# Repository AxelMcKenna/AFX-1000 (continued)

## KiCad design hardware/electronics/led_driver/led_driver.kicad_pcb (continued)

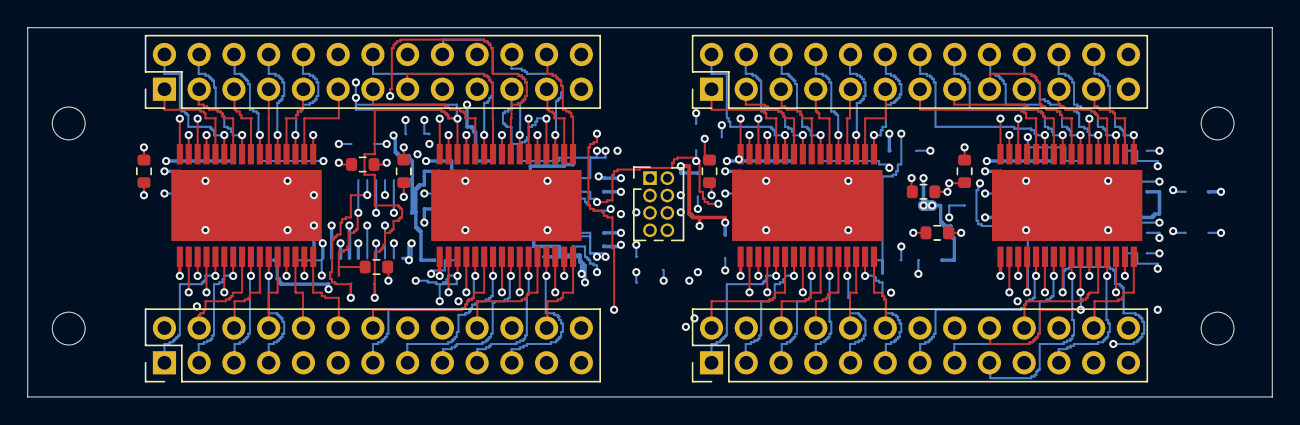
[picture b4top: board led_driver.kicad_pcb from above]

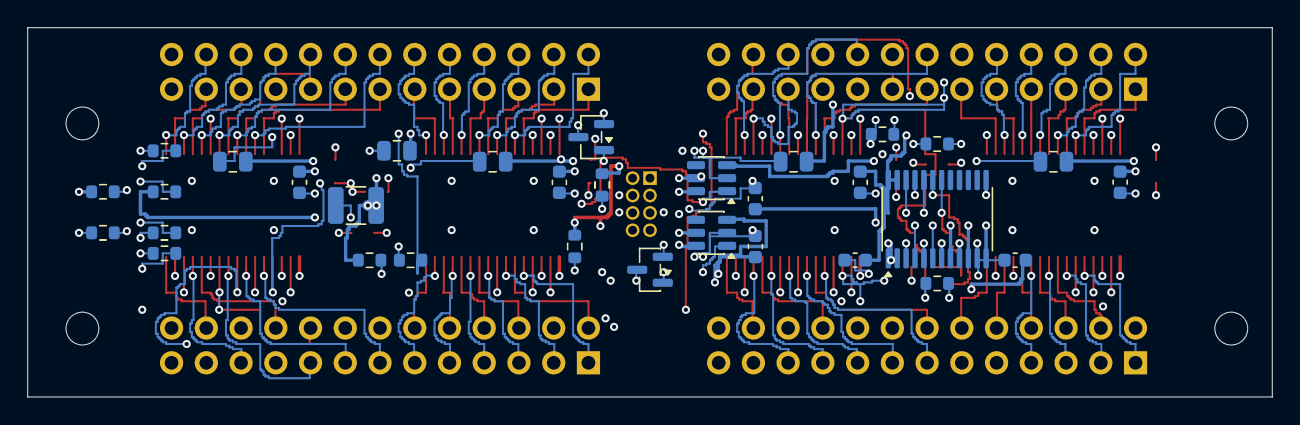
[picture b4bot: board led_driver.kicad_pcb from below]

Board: 6 copper layers, 91.0 x 27.0 mm, 53 parts (32 on the bottom side), 122 nets.

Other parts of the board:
H1, H2, H3, H4: M2_CLEARANCE; M2_Insert_Clearance

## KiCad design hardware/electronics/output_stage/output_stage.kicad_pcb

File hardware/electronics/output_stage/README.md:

# E05 circuit / E07 routed stereo output board

E05 is the native KiCad schematic for the post-receiver line drivers and stereo
gain-output relay: 41 components, fixed-feedback master/consumer amplifiers,
separate coupling/bleed networks and the E02/E03 interfaces. E07 is a **routed,
unassembled output-stage prototype**, not the complete analog/power design.

The [native E07 PCB](output_stage.kicad_pcb) is 82 × 34 × 1.6 mm with four copper
layers, 211 track segments and 45 through vias. The
[routing check](generated/routing-verification.json) passes all-severity native
DRC/library/parity with **zero violations and zero open connections**. KiCad
refills and saves the analog reference plane before the check. Native
[top](generated/placement-top.svg), [bottom](generated/placement-bottom.svg),
[reference plane](generated/reference-plane.svg) and
[inner routing](generated/inner-routing.svg) views show the actual saved board.
This electrical layout check does not establish fabrication readiness or audio
performance; final stackup, passive/connector selection and bench work remain open.

Open [the native project](output_stage.kicad_pro),
[schematic SVG](generated/output_stage.svg), [BOM](bom.csv),
[connection schedule](components.json) or
[verification record](generated/verification.json). The
[circuit analysis](generated/circuit-analysis.json) uses the actual exported
netlist and explicitly identifies its ideal-device assumptions.
The [A03/E07 review package](../../cad/generated/standalone-review-A03-E07.zip)
includes the current hardware sources, native projects, CAD and check records.
Standard KiCad/OpenSCAD and the documented Python packages remain external.

## Circuit and boundary

J1 requires a low-impedance, nominal 2 V RMS full-scale **single-ended** signal
nominally centered on 0 V after the DAC's I/V and differential receiver/filter.
It is not an interface to the raw codec differential pins. The
[E08 receiver prototype](../dac_receiver/README.md) proposes a ±25 mV DC
allocation and checks that allowance against the E05 peak-margin screen. The
original ideal E05 calculations use zero DC; physical scale, calibration and
power behavior remain unverified. Keep its source impedance
at or below 100 Ω; R17/R18 provide 100 kΩ bias returns.

Both drivers run continuously. U1, OPA2992D on regulated ±19 V, supplies Master
gain 6.23 using 5.23 kΩ/1 kΩ feedback. U2, OPA1612AID on regulated ±12 V, supplies
Send/Return gain 1.605 using 1.21 kΩ/2 kΩ feedback. The consumer resistor scale
keeps the feedback and output loads together above 2 kΩ. Feedback stays connected
regardless of the gain relay position.

Each branch has 100 Ω series resistance, two parallel 4.7 µF nonpolar film
capacitors and a 20 kΩ discharge resistor. K3 selects Master through its NC
contacts or Send/Return through its NO contacts; it never directly joins the
two amplifier outputs. Separate coupling networks let both branches retain
their own DC settling. Capacitors block DC in the ideal model; leakage,
dielectric behavior and switching transients require measurement.

| Interface | Pins / connection |
| --- | --- |
| J1 post-receiver input | 1:Left, 2:AGND, 3:Right; 2 V RMS nominal full scale, zero DC |
| J2 processed output | 1:Left, 2:AGND, 3:Right → E03 J3 pins 4/5/6 |
| J3 gain coil | 1:5 V, 2:GAIN_LOW → E02 J5 pins 1/2 |
| J4 regulated supplies | 1:+19 V, 2:AGND, 3:−19 V, 4:+12 V, 5:−12 V |

The second gain relay, for stereo input-range selection, is external and must
share E02's gain driver as planned. Firmware D9 stays low for Master and high
for Send/Return; the existing dry-wait/gain-settle/rearm sequence still applies.
This sheet does not contain a second driver or another flyback clamp.

**All four analog rails** must qualify E02 ANALOG_OK, independently of firmware.
Loss of the ±12 V pair can invalidate the selected consumer output and receiver
even if ±19 V remains healthy. Exact supervisors, thresholds, sequencing and
power-down margins remain unselected. Use the digital/power return for the coil
current; resolve analog reference and shield connections in the integrated PCB.

±12 V gives the low-voltage receiver/driver domain room for the prospective ADC
driver; its final load remains to be calculated. This choice does not approve
the complete analog power budget. OPA1612 must not use the ±19 V rails.

## Calculated results and limits

With nominal parts, an ideal 2 V RMS input and a combined external 10 kΩ load:

| Result | Master | Send/Return |
| --- | ---: | ---: |
| Output at 1 kHz | 12.276 V RMS | 3.163 V RMS |
| Scale error against E01 target | −0.0050 dB | +0.0008 dB |
| Effective amplifier resistive load | 3.244 kΩ | 2.177 kΩ |
| Passive coupling loss at 20 Hz relative to 1 kHz | −0.0674 dB | −0.0674 dB |

The 20 kΩ bleed and the external load are both included. Tolerance analysis
enumerates all 64 sign combinations per branch, 256 total: 0.1% feedback/ground,
1% series/bleed and 10% for each coupling capacitor. At a fixed 10 kΩ external
load, calculated scale error stays within 0.022 dB, the passive 20 Hz coupling
loss stays below 0.084 dB and the amplifier load remains above 2 kΩ.

These are output-stage calculations. Receiver scale/loading and the full unit's
gain error are not verified. The 10 kΩ limit is the **combined** external load
of all parallel output connectors; smaller loads need a new review.

The rail screen includes 1% supply tolerance, worst feedback tolerances and a
1% high full-scale input. It leaves about 0.68 V of peak margin for Master with
an assumed 0.3 V amplifier rail reserve. That reserve is from OPA2992's 40 V/2 kΩ
table; its use at the planned 38 V supply is still a screening assumption.
The consumer screen uses OPA1612's 0.6 V reserve at 2 kΩ. Neither establishes
real clipping, distortion or capacitive-load stability.

The illustrative white-density output-noise estimates are approximately
6.88 µV RMS for Master and 0.89 µV for Send/Return over 20 Hz–20 kHz, unweighted.
They include passive coupling and bleed noise but omit 1/f noise, receiver/source
noise, supplies, PCB coupling and part spread. Do not combine these directly
with A-weighted codec figures or claim a passing whole-unit S/N result.

An ideal class-B/quiescent-power screen gives approximately 0.26 W for the
master dual package and 0.29 W for the consumer dual package. Reference thermal
resistances imply substantial temperature rise; actual board copper, airflow,
internal ambient and temperatures remain to be measured. There is no validated
short-circuit or overload rating for the output resistors or complete stage.

## Capacitors and housing impact

The reviewed WIMA MKS2 drawing is revision 03.26. It lists
MKS2C044701O00KSSD, 4.7 µF/63 V/10%, with a 7.2 × 11 × 18 mm nominal body,
5 mm lead pitch and nominal 0.5 mm leads. Each branch uses two in parallel for
9.4 µF. The earlier 10 µF/50 V part is absent from this current drawing and is
not used in E05. The [source record](dependencies.json) captures the PDF hash.

The standard footprint's actual 5 mm pitch and 0.8 mm drill are checked. Its
nominal plan size is a candidate; maximum body/lead tolerances, standoff,
courtyard and printed assembly still need fit checks. Its generic 3D model does
not prove the 18 mm height. The former A02 12 mm audio reserve did not contain
these parts. A03 now uses the E07 placement packet, lowers the board to Z=3.8,
adds a floor recess and staggers the capacitor pairs to clear scene controls.
The [CAD report](../../cad/generated/solid-validation.json) records empty
intersection with the modeled shell/controls, including switch-lead and
scene-PCB allowances. This remains conditional on the documented dimensions
and assembly limits, with physical fit unverified.

The [actual-PCB mechanical packet](generated/placement.json) includes all 41
component and 29 through-hole solder/lead reserves. The four series resistors,
four bleed resistors and C8 sit on the back. Trim through-hole protrusions,
including solder, to ≤1.5 mm. Qualify the underside resistor/capacitor height
limits and the remaining generic passive MPNs before assembly.

Four Ø2.4 mounting holes match the CAD's Ø7.2 bosses and Ø3.2 through bores for
CNC Kitchen M2 × 3 inserts. Through bores accommodate the short boss stack; the
insert is flush, with M2 × 4 board screws. The floor recess leaves 1.6 mm of
plastic. Actual bore/insert fit, wall/floor stiffness and screw engagement remain
physical checks. The converter/input and final power-board placements are open.

## Native checks and remaining integration

Routing is explicit in [route.py](route.py). Feedback stays on the top layer
near the amplifiers; the four coupled branches stay separate until K3. R10
moves down to avoid taking its ground pad across the consumer-left feedback
path. F.Cu/B.Cu carry most audio traces, In1.Cu is the AGND reference plane,
and In2.Cu carries the inputs, supply trunks, a short output crossing and the
separate two-wire coil circuit. Coil current returns only through E02's driver.
The routing uses 0.3–0.6 mm tracks and Ø0.7/0.3 mm through vias, with a 0.25 mm
minimum clearance. No blind vias, via-in-pad assembly process or buried vias are
required. The fabrication house's actual four-layer materials and copper weights
are still to be selected; the present 1.6 mm thickness is a mechanical contract.

Local bypasses follow the amplifier supply pins. The longer signal paths,
single reference plane, return currents, supply impedance, thermal behavior and
coil switching still require review and measurement on the assembled board.
Native DRC does not verify signal integrity, stability, S/N or switching clicks.

    python3 -m hardware.electronics.output_stage.generate
    python3 -m hardware.electronics.output_stage.place --kicad-cli /path/to/kicad-cli
    python3 -m hardware.electronics.output_stage.route
    python3 -m hardware.electronics.output_stage.verify --kicad-cli /path/to/kicad-cli
    python3 -m hardware.electronics.output_stage.check_placement --kicad-cli /path/to/kicad-cli
    python3 -m hardware.cad.standalone

The verifier runs all-severity native KiCad ERC and checks every exported pin
against an independent contract. Fresh E02/E03 exports confirm the harnesses.
A complex nodal solver checks both channels and both relay states at 20 Hz,
1 kHz and 20 kHz: 12 ideal AC cases, with four further ideal DC-blocking cases.
The analytical gain/filter expressions are compared against that circuit solve.
The checks do not run a semiconductor SPICE model or measure real crosstalk.

Standard libraries remain external; --footprint-dir can locate them. Source and
library hashes are recorded. Generation replaces the native schematic, so
persist circuit edits in generate.py while using this workflow.
Persist footprint positions and board datums in place.py. It regenerates the
board and overwrites direct PCB edits. route.py adds/replaces generated copper;
it accepts both the initial legacy file and KiCad 10's normalized saved file.
check_placement.py refills/saves the actual board, requires all native DRC/parity
and connectivity results to be clear, and exports the mechanical packet;
standalone.py rejects
a packet whose PCB hash is stale. Standard footprints are embedded in the PCB
as in a normal KiCad board; their external libraries are not vendored. The local
mounting footprint is original project geometry. For a deliberately placed-only
intermediate, check_placement.py --unrouted retains and reports open connections;
it cannot label that state as routed. The earlier placement-drc.json is retained
as historical E06 evidence; routing-drc.json is the current native result.

Complete the converter/receiver, stereo input protection/range stage, regulators,
all rail supervisors, final connectors, ESD and integrated PCB before fabrication.
Then measure frequency response, calibrated gain, noise/THD, clipping, DC/clicks,
hot-plug, capacitive loads, output shorts, power loss and actual temperatures.
Prototype header footprints, some passive MPNs and capacitor bias curves remain
selection gates. E07 routing is complete for this output subassembly. No board
has been ordered, fabricated, assembled or released as the complete unit.

Primary sources: [OPA2992](https://www.ti.com/lit/ds/symlink/opa2992.pdf),
[OPA1612](https://www.ti.com/lit/ds/symlink/opa1612.pdf),
[WIMA MKS2](https://wima.de/wp-content/uploads/media/e_WIMA_MKS_2.pdf),
[Omron G6K](https://omronfs.omron.com/en_US/ecb/products/pdf/en-g6k.pdf).

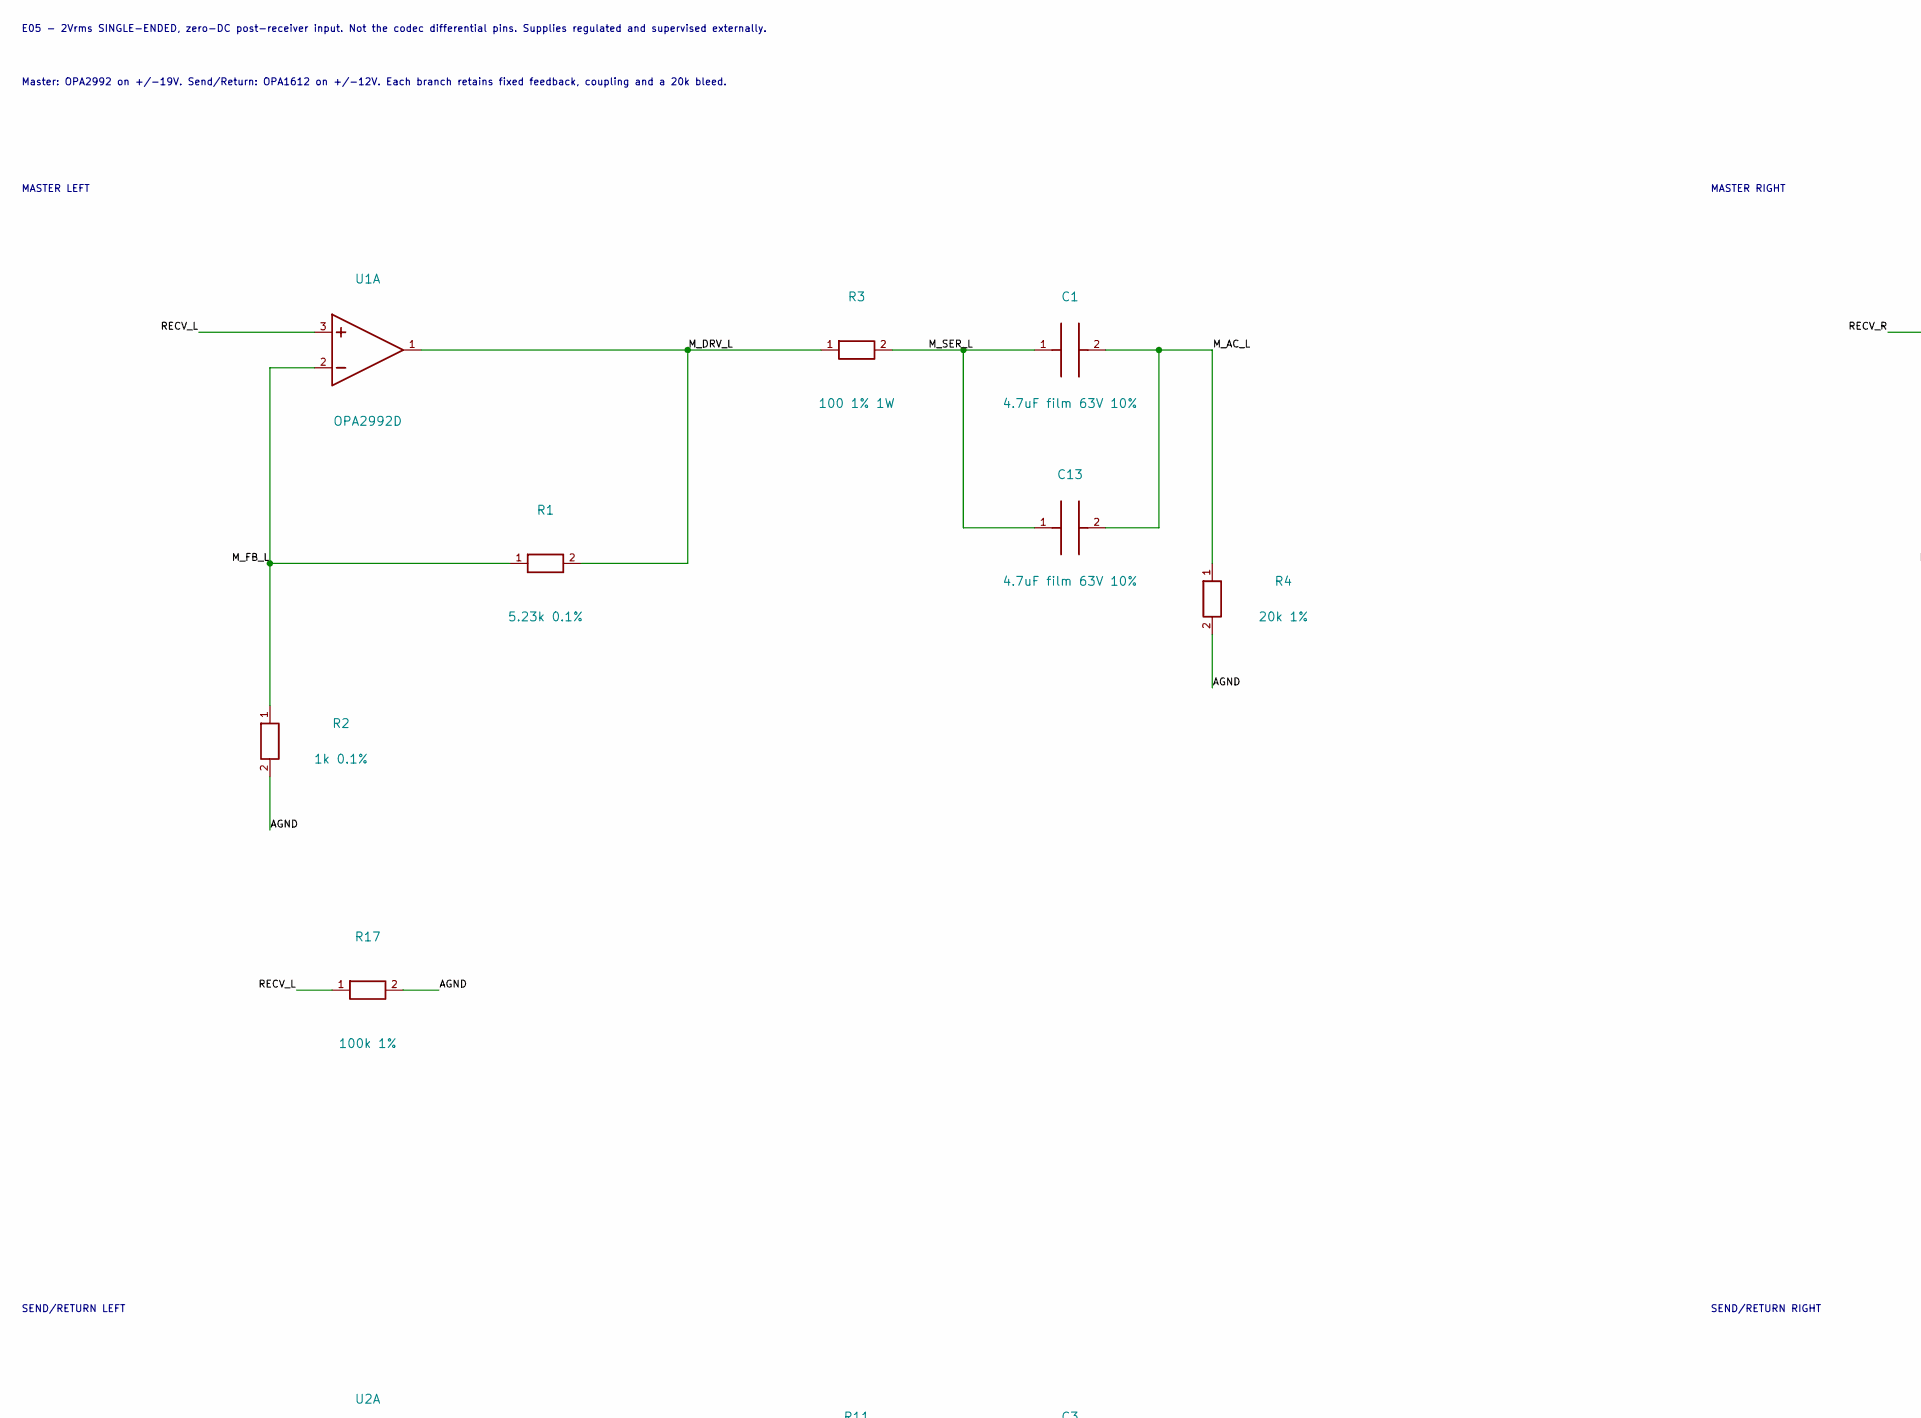
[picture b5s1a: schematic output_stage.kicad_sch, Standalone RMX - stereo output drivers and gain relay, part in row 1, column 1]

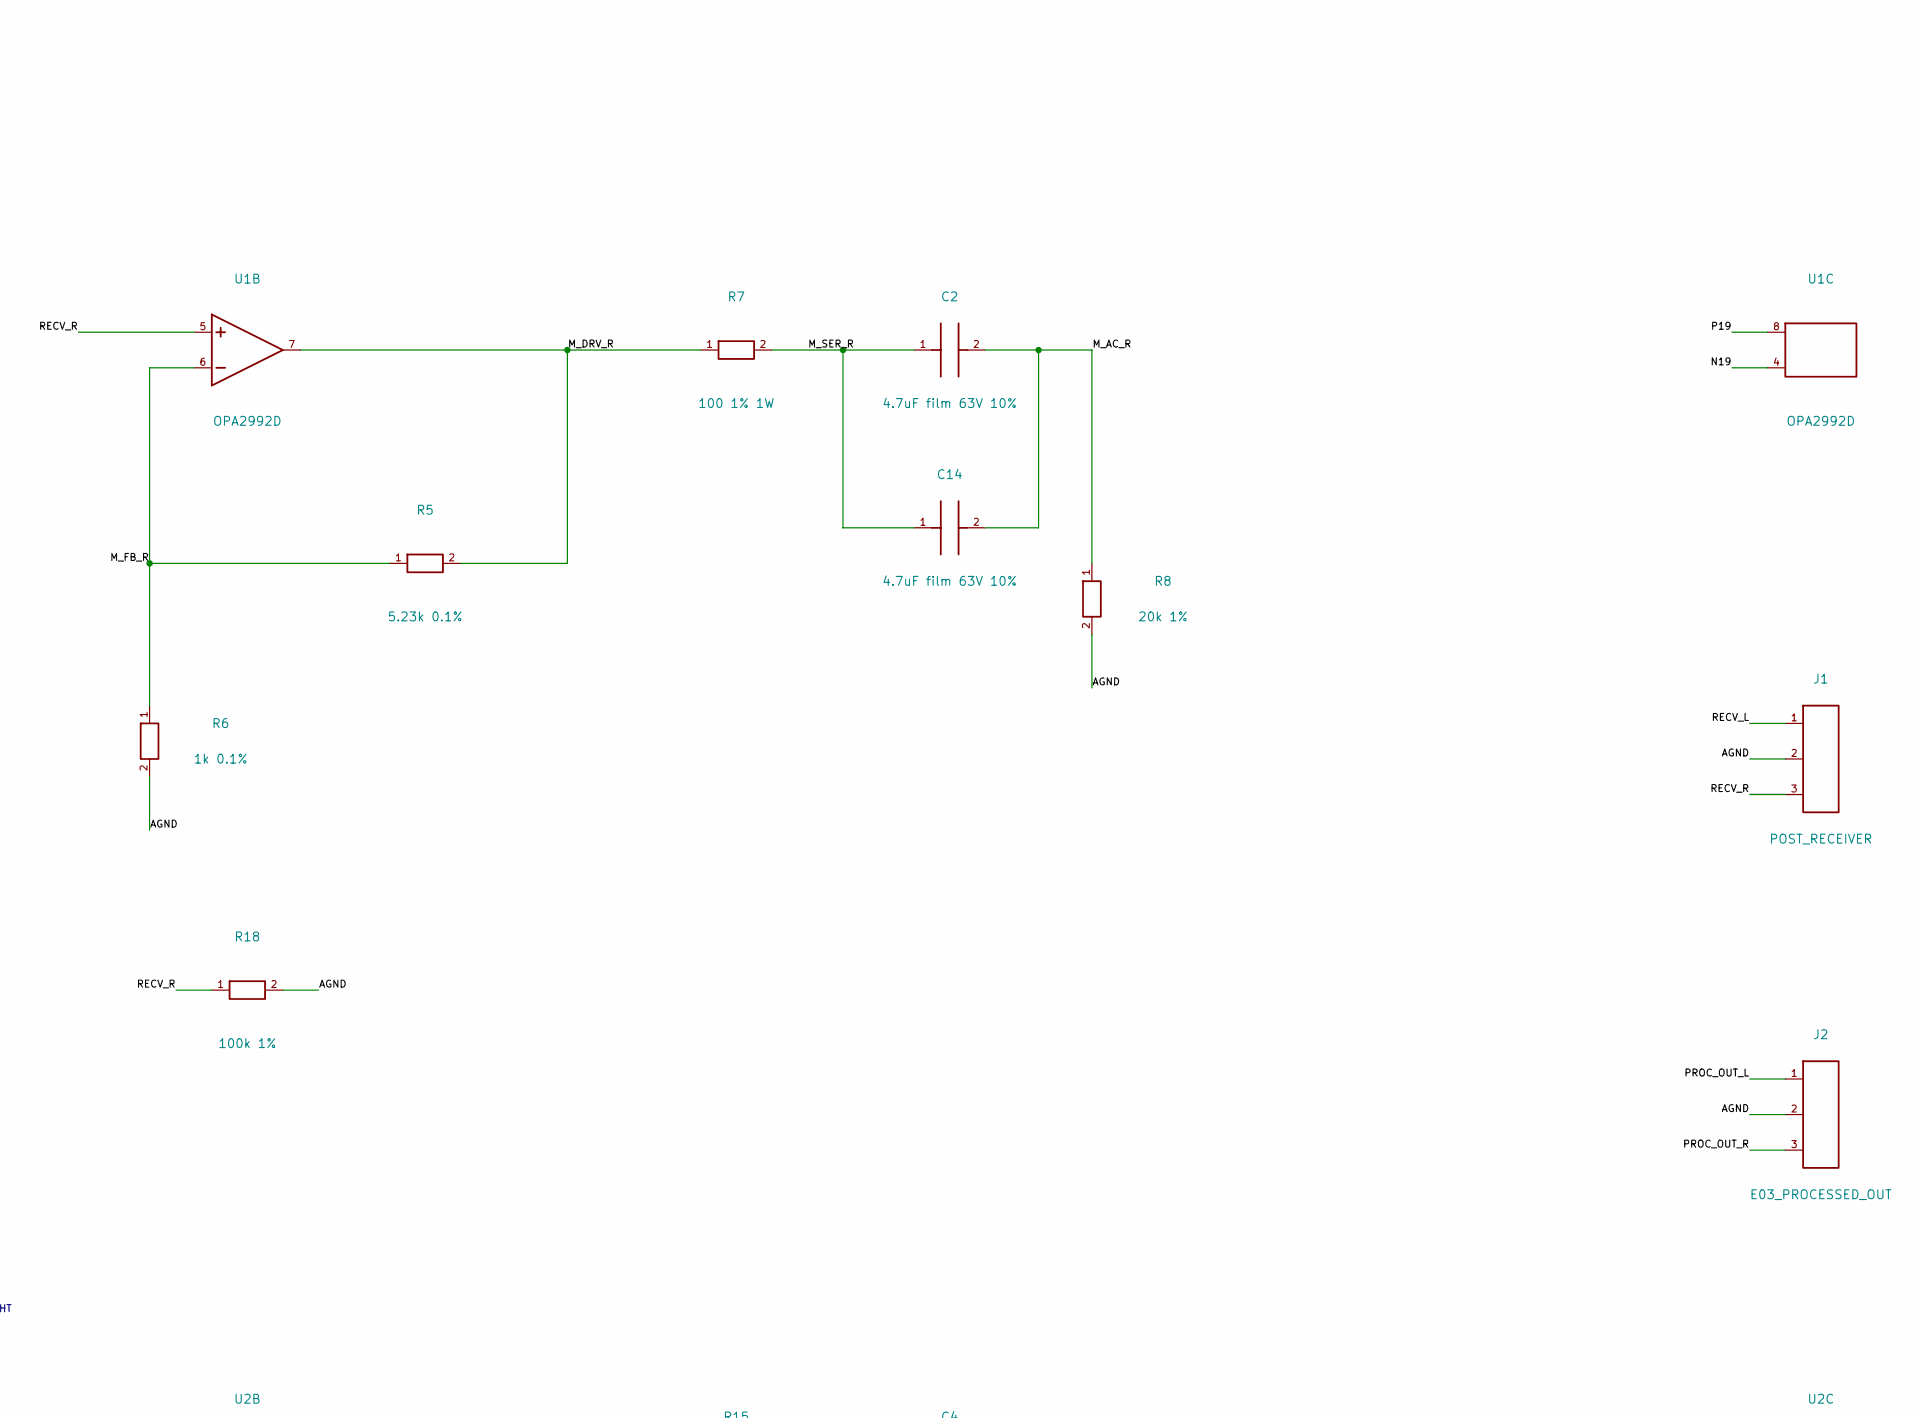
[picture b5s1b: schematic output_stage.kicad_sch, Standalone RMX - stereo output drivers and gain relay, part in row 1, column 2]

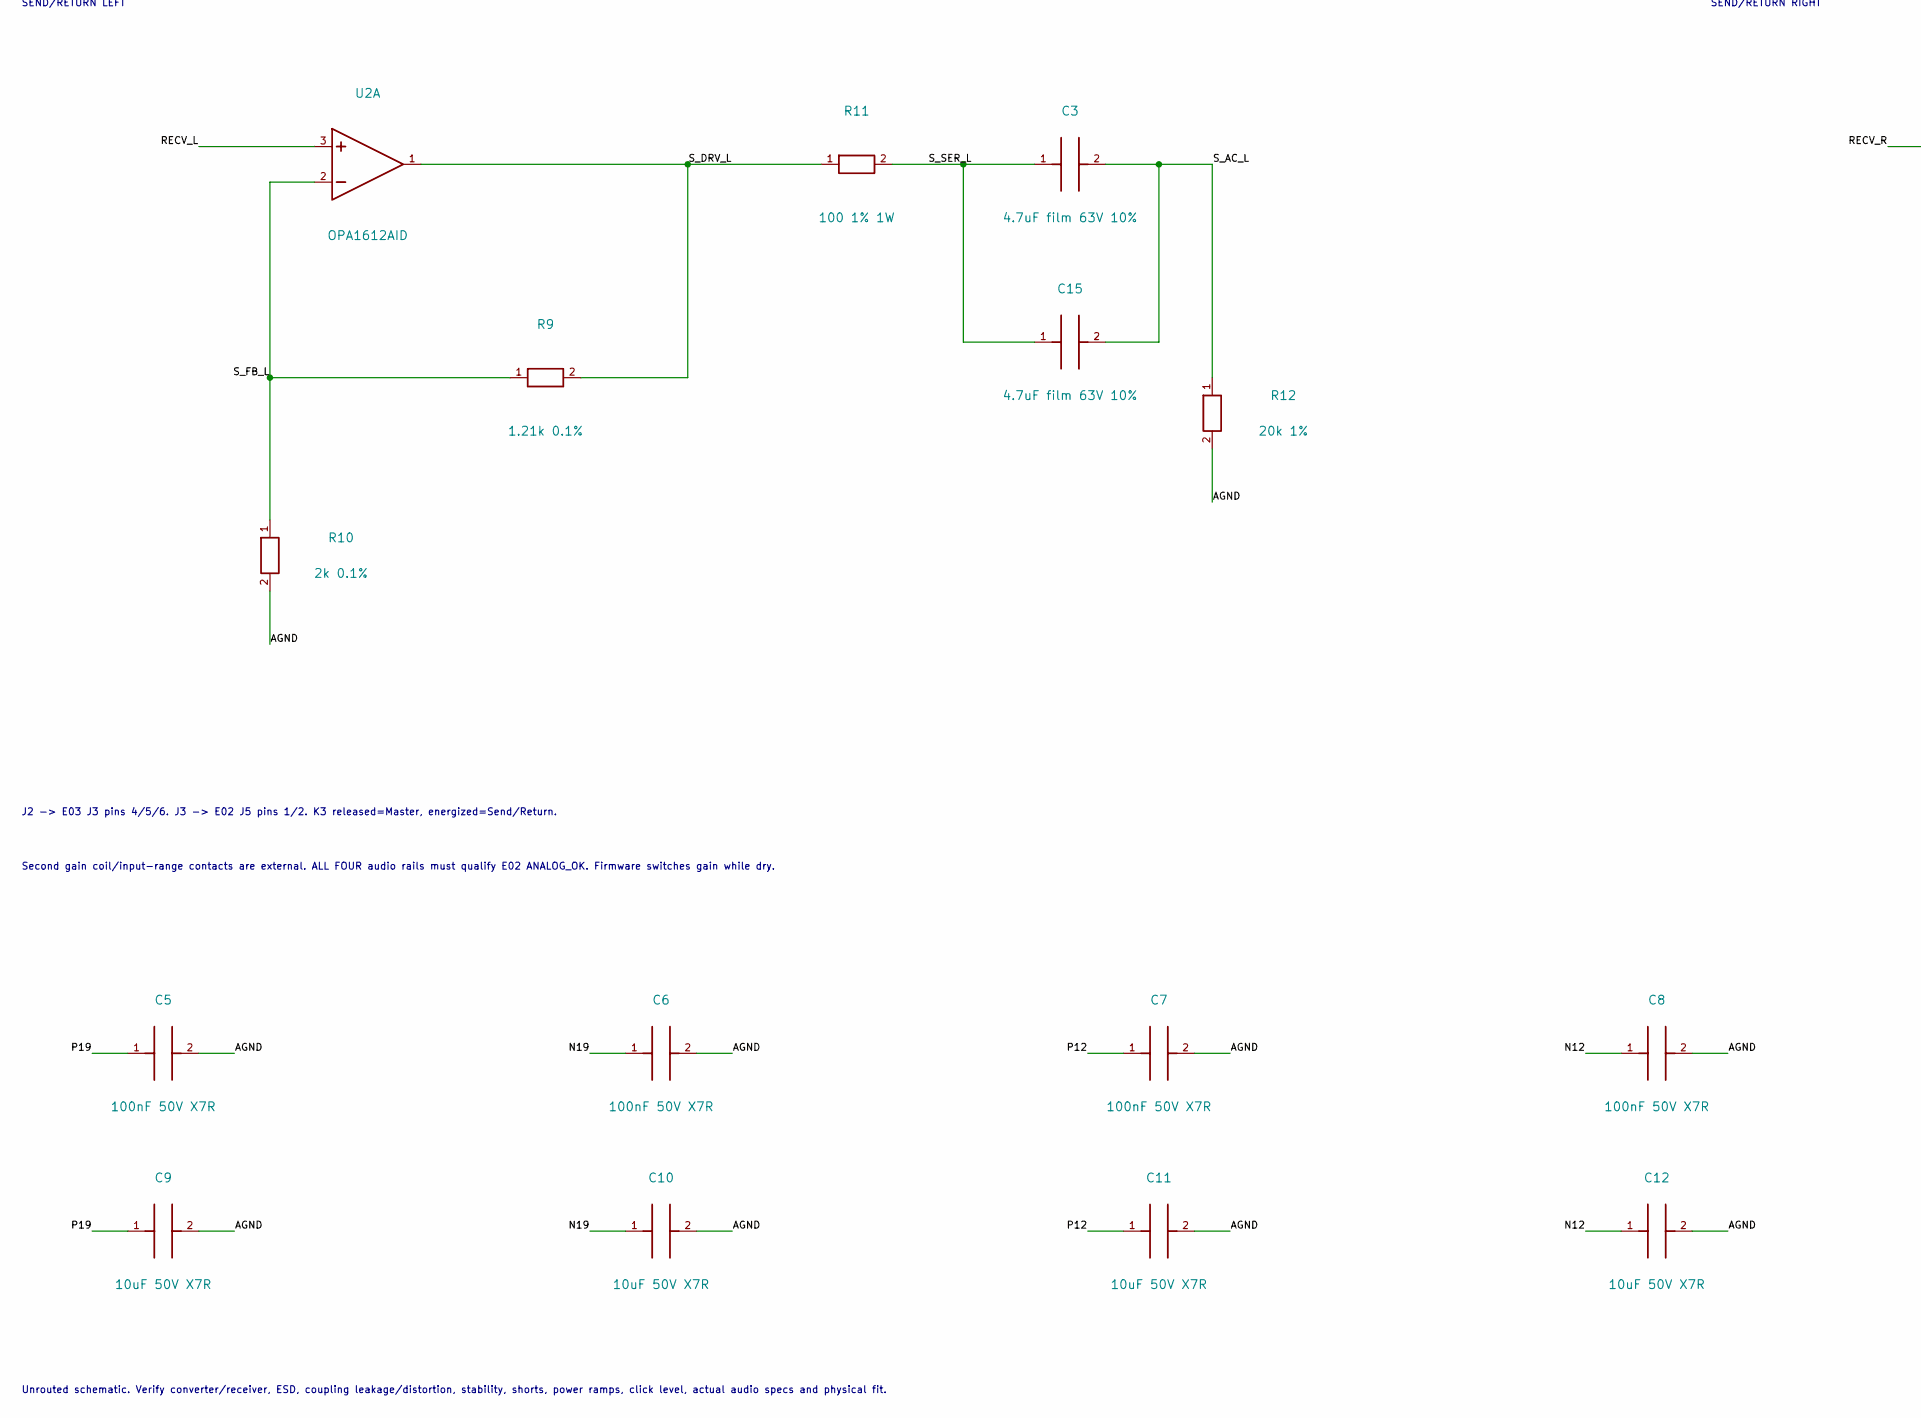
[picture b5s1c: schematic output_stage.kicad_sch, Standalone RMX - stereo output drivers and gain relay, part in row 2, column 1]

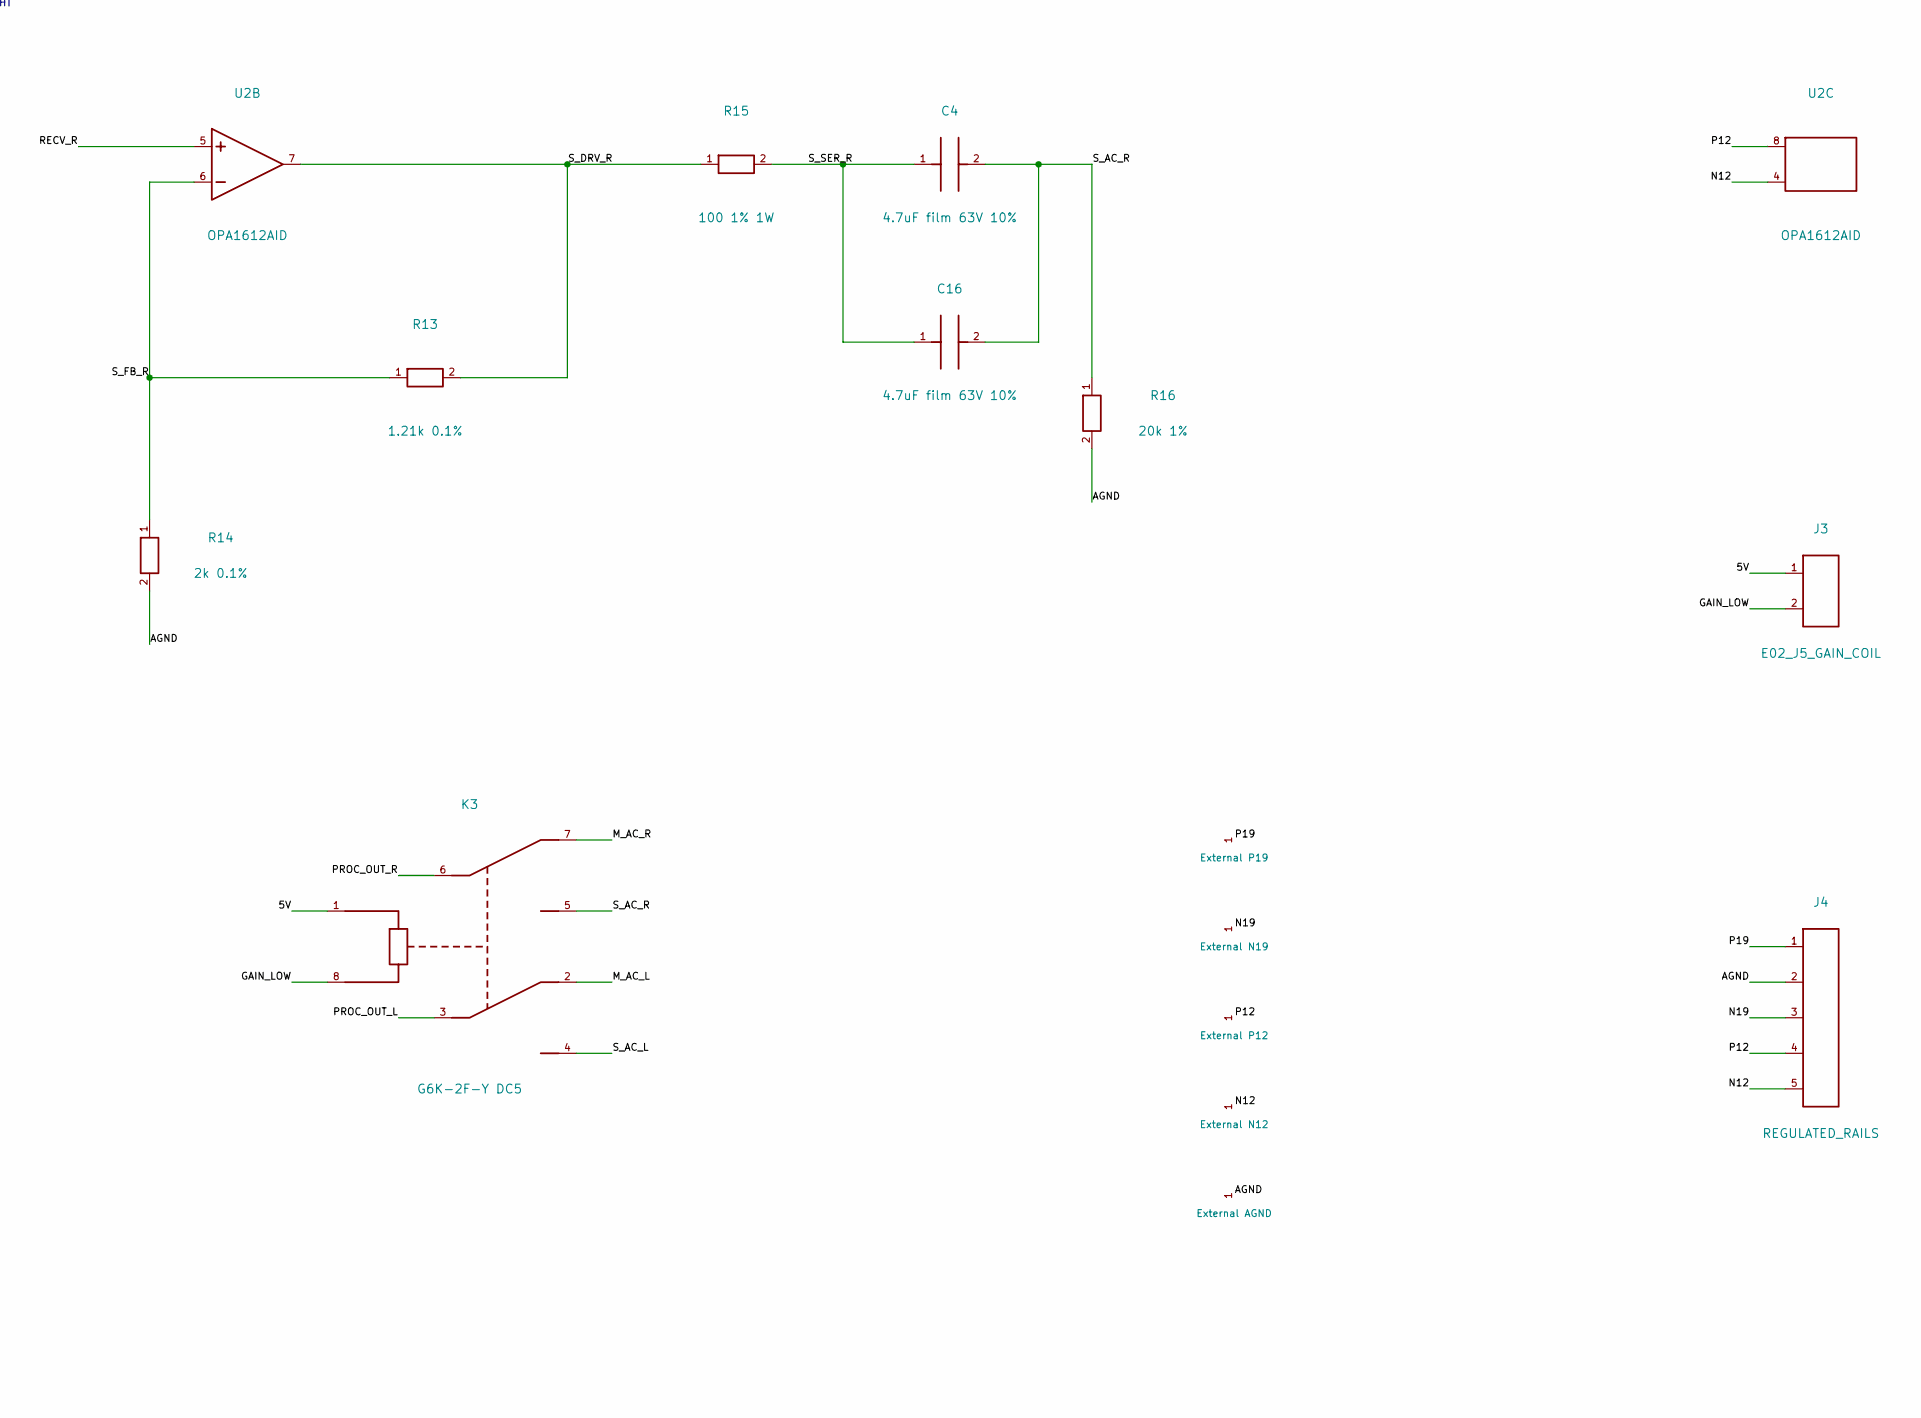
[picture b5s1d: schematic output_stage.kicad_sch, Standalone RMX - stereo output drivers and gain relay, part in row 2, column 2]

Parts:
C1, C2, C3, C4, C13, C14, C15, C16: 4.7uF film 63V 10%; C_Rect_L7.2mm_W11.0mm_P5.00mm_FKS2_FKP2_MKS2_MKP2; MPN MKS2C044701O00KSSD
C5, C6, C7, C8: 100nF 50V X7R; C_0805_2012Metric
C9, C10, C11, C12: 10uF 50V X7R; C_1210_3225Metric
J1: POST_RECEIVER; PinHeader_1x03_P2.54mm_Vertical
J2: E03_PROCESSED_OUT; PinHeader_1x03_P2.54mm_Vertical
J3: E02_J5_GAIN_COIL; PinHeader_1x02_P2.54mm_Vertical
J4: REGULATED_RAILS; PinHeader_1x05_P2.54mm_Vertical
K3: G6K-2F-Y DC5; Relay_DPDT_Omron_G6K-2F-Y; MPN G6K-2F-Y DC5
R1, R5: 5.23k 0.1%; R_0805_2012Metric
R2, R6: 1k 0.1%; R_0805_2012Metric
R3, R7, R11, R15: 100 1% 1W; R_2512_6332Metric
R4, R8, R12, R16: 20k 1%; R_0805_2012Metric
R9, R13: 1.21k 0.1%; R_0805_2012Metric
R10, R14: 2k 0.1%; R_0805_2012Metric
R17, R18: 100k 1%; R_0805_2012Metric
U1: OPA2992D; SOIC-8_3.9x4.9mm_P1.27mm; MPN OPA2992D
U2: OPA1612AID; SOIC-8_3.9x4.9mm_P1.27mm; MPN OPA1612AID

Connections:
/5V: J3.1, K3.1 (COIL+)
/AGND: C5.2, C6.2, C7.2, C8.2, C9.2, C10.2, C11.2, C12.2, J1.2, J2.2, J4.2, R2.2, R4.2, R6.2, R8.2, R10.2, R12.2, R14.2, R16.2, R17.2, R18.2
/GAIN_LOW: J3.2, K3.8 (COIL-)
/M_AC_L: C1.2, C13.2, K3.2 (L_NC), R4.1
/M_AC_R: C2.2, C14.2, K3.7 (R_NC), R8.1
/M_DRV_L: R1.2, R3.1, U1.1 (OUT)
/M_DRV_R: R5.2, R7.1, U1.7 (OUT)
/M_FB_L: R1.1, R2.1, U1.2 (-)
/M_FB_R: R5.1, R6.1, U1.6 (-)
/M_SER_L: C1.1, C13.1, R3.2
/M_SER_R: C2.1, C14.1, R7.2
/N12: C8.1, C12.1, J4.5, U2.4 (V-)
/N19: C6.1, C10.1, J4.3, U1.4 (V-)
/P12: C7.1, C11.1, J4.4, U2.8 (V+)
/P19: C5.1, C9.1, J4.1, U1.8 (V+)
/PROC_OUT_L: J2.1, K3.3 (L_COM)
/PROC_OUT_R: J2.3, K3.6 (R_COM)
/RECV_L: J1.1, R17.1, U1.3 (+), U2.3 (+)
/RECV_R: J1.3, R18.1, U1.5 (+), U2.5 (+)
/S_AC_L: C3.2, C15.2, K3.4 (L_NO), R12.1
/S_AC_R: C4.2, C16.2, K3.5 (R_NO), R16.1
/S_DRV_L: R9.2, R11.1, U2.1 (OUT)
/S_DRV_R: R13.2, R15.1, U2.7 (OUT)
/S_FB_L: R9.1, R10.1, U2.2 (-)
/S_FB_R: R13.1, R14.1, U2.6 (-)
/S_SER_L: C3.1, C15.1, R11.2
/S_SER_R: C4.1, C16.1, R15.2

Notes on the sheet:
E05 - 2Vrms SINGLE-ENDED, zero-DC post-receiver input. Not the codec differential pins. Supplies regulated and supervised externally.
Master: OPA2992 on +/-19V. Send/Return: OPA1612 on +/-12V. Each branch retains fixed feedback, coupling and a 20k bleed.
MASTER LEFT
MASTER RIGHT
SEND/RETURN LEFT
SEND/RETURN RIGHT
J2 -> E03 J3 pins 4/5/6. J3 -> E02 J5 pins 1/2. K3 released=Master, energized=Send/Return.
Second gain coil/input-range contacts are external. ALL FOUR audio rails must qualify E02 ANALOG_OK. Firmware switches gain while dry.
Unrouted schematic. Verify converter/receiver, ESD, coupling leakage/distortion, stability, shorts, power ramps, click level, actual audio specs and physical fit.

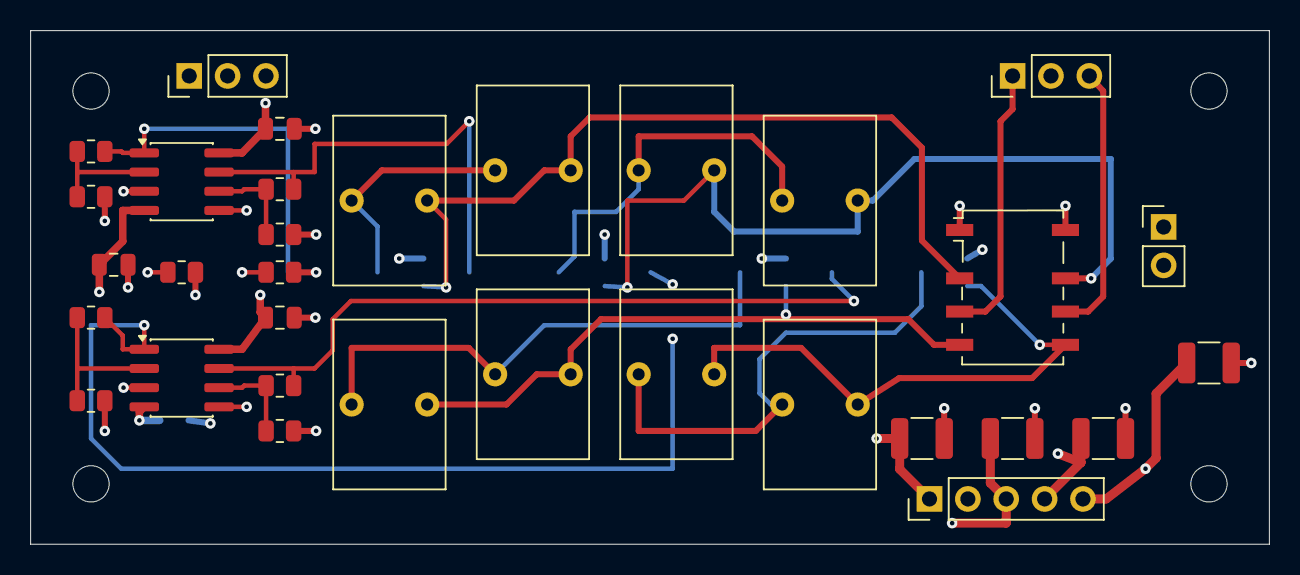
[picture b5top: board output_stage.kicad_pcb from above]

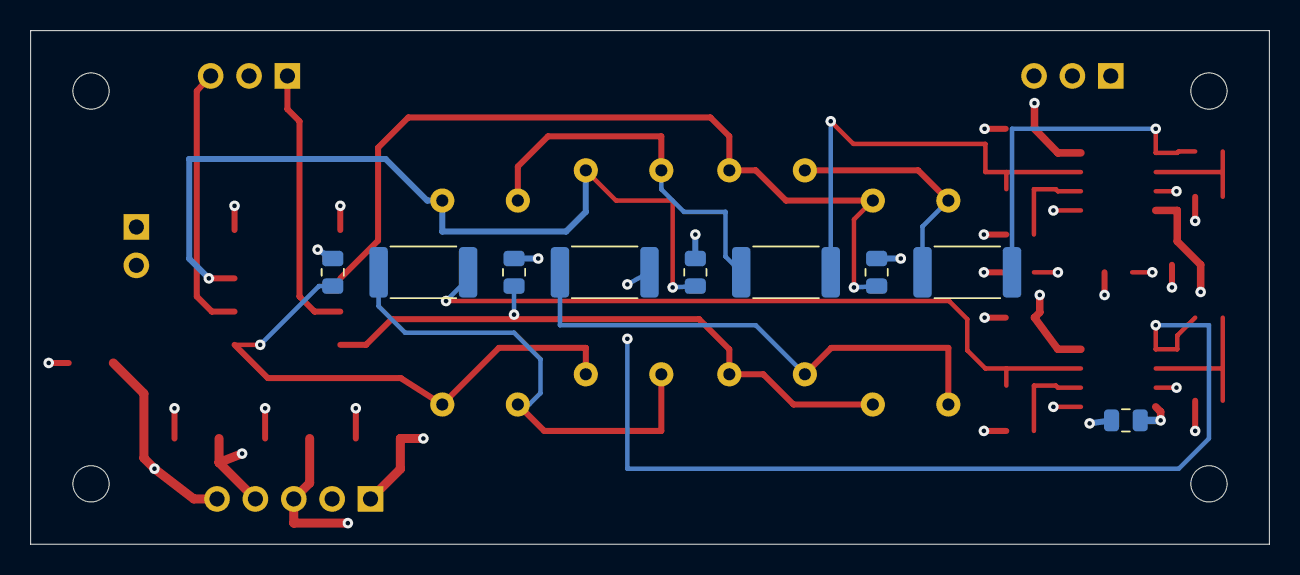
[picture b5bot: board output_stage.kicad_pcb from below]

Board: 4 copper layers, 82.0 x 34.0 mm, 45 parts (9 on the bottom side), 27 nets.

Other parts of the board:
H1, H2, H3, H4: M2_CLEARANCE; M2_Insert_Clearance

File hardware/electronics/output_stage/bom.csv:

ref,value,mpn,footprint,source,note
U1,OPA2992D,OPA2992D,Package_SO:SOIC-8_3.9x4.9mm_P1.27mm,https://www.ti.com/lit/ds/symlink/opa2992.pdf,
U2,OPA1612AID,OPA1612AID,Package_SO:SOIC-8_3.9x4.9mm_P1.27mm,https://www.ti.com/lit/ds/symlink/opa1612.pdf,
R1,5.23k 0.1%,,Resistor_SMD:R_0805_2012Metric,,
R2,1k 0.1%,,Resistor_SMD:R_0805_2012Metric,,
R3,100 1% 1W,,Resistor_SMD:R_2512_6332Metric,,Normal-load rating only; short/transient and thermal behavior unverified
R4,20k 1%,,Resistor_SMD:R_0805_2012Metric,,
C1,4.7uF film 63V 10%,MKS2C044701O00KSSD,Capacitor_THT:C_Rect_L7.2mm_W11.0mm_P5.00mm_FKS2_FKP2_MKS2_MKP2,https://wima.de/wp-content/uploads/media/e_WIMA_MKS_2.pdf,"Nonpolar PET; nominal body 7.2 x 11 x 18mm, pitch 5mm; 9.4uF per parallel pair; physical fit unverified"
C13,4.7uF film 63V 10%,MKS2C044701O00KSSD,Capacitor_THT:C_Rect_L7.2mm_W11.0mm_P5.00mm_FKS2_FKP2_MKS2_MKP2,https://wima.de/wp-content/uploads/media/e_WIMA_MKS_2.pdf,"Nonpolar PET; nominal body 7.2 x 11 x 18mm, pitch 5mm; 9.4uF per parallel pair; physical fit unverified"
R5,5.23k 0.1%,,Resistor_SMD:R_0805_2012Metric,,
R6,1k 0.1%,,Resistor_SMD:R_0805_2012Metric,,
R7,100 1% 1W,,Resistor_SMD:R_2512_6332Metric,,Normal-load rating only; short/transient and thermal behavior unverified
R8,20k 1%,,Resistor_SMD:R_0805_2012Metric,,
C2,4.7uF film 63V 10%,MKS2C044701O00KSSD,Capacitor_THT:C_Rect_L7.2mm_W11.0mm_P5.00mm_FKS2_FKP2_MKS2_MKP2,https://wima.de/wp-content/uploads/media/e_WIMA_MKS_2.pdf,"Nonpolar PET; nominal body 7.2 x 11 x 18mm, pitch 5mm; 9.4uF per parallel pair; physical fit unverified"
C14,4.7uF film 63V 10%,MKS2C044701O00KSSD,Capacitor_THT:C_Rect_L7.2mm_W11.0mm_P5.00mm_FKS2_FKP2_MKS2_MKP2,https://wima.de/wp-content/uploads/media/e_WIMA_MKS_2.pdf,"Nonpolar PET; nominal body 7.2 x 11 x 18mm, pitch 5mm; 9.4uF per parallel pair; physical fit unverified"
R9,1.21k 0.1%,,Resistor_SMD:R_0805_2012Metric,,
R10,2k 0.1%,,Resistor_SMD:R_0805_2012Metric,,
R11,100 1% 1W,,Resistor_SMD:R_2512_6332Metric,,Normal-load rating only; short/transient and thermal behavior unverified
R12,20k 1%,,Resistor_SMD:R_0805_2012Metric,,
C3,4.7uF film 63V 10%,MKS2C044701O00KSSD,Capacitor_THT:C_Rect_L7.2mm_W11.0mm_P5.00mm_FKS2_FKP2_MKS2_MKP2,https://wima.de/wp-content/uploads/media/e_WIMA_MKS_2.pdf,"Nonpolar PET; nominal body 7.2 x 11 x 18mm, pitch 5mm; 9.4uF per parallel pair; physical fit unverified"
C15,4.7uF film 63V 10%,MKS2C044701O00KSSD,Capacitor_THT:C_Rect_L7.2mm_W11.0mm_P5.00mm_FKS2_FKP2_MKS2_MKP2,https://wima.de/wp-content/uploads/media/e_WIMA_MKS_2.pdf,"Nonpolar PET; nominal body 7.2 x 11 x 18mm, pitch 5mm; 9.4uF per parallel pair; physical fit unverified"
R13,1.21k 0.1%,,Resistor_SMD:R_0805_2012Metric,,
R14,2k 0.1%,,Resistor_SMD:R_0805_2012Metric,,
R15,100 1% 1W,,Resistor_SMD:R_2512_6332Metric,,Normal-load rating only; short/transient and thermal behavior unverified
R16,20k 1%,,Resistor_SMD:R_0805_2012Metric,,
C4,4.7uF film 63V 10%,MKS2C044701O00KSSD,Capacitor_THT:C_Rect_L7.2mm_W11.0mm_P5.00mm_FKS2_FKP2_MKS2_MKP2,https://wima.de/wp-content/uploads/media/e_WIMA_MKS_2.pdf,"Nonpolar PET; nominal body 7.2 x 11 x 18mm, pitch 5mm; 9.4uF per parallel pair; physical fit unverified"
C16,4.7uF film 63V 10%,MKS2C044701O00KSSD,Capacitor_THT:C_Rect_L7.2mm_W11.0mm_P5.00mm_FKS2_FKP2_MKS2_MKP2,https://wima.de/wp-content/uploads/media/e_WIMA_MKS_2.pdf,"Nonpolar PET; nominal body 7.2 x 11 x 18mm, pitch 5mm; 9.4uF per parallel pair; physical fit unverified"
R17,100k 1%,,Resistor_SMD:R_0805_2012Metric,,Input cable bias return; receiver must supply <=100Ohm source impedance
R18,100k 1%,,Resistor_SMD:R_0805_2012Metric,,Input cable bias return; receiver must supply <=100Ohm source impedance
C5,100nF 50V X7R,,Capacitor_SMD:C_0805_2012Metric,,
C9,10uF 50V X7R,,Capacitor_SMD:C_1210_3225Metric,,Require effective capacitance >=4.7uF on actual rail; exact MPN/bias curve unselected
C6,100nF 50V X7R,,Capacitor_SMD:C_0805_2012Metric,,
C10,10uF 50V X7R,,Capacitor_SMD:C_1210_3225Metric,,Require effective capacitance >=4.7uF on actual rail; exact MPN/bias curve unselected
C7,100nF 50V X7R,,Capacitor_SMD:C_0805_2012Metric,,
C11,10uF 50V X7R,,Capacitor_SMD:C_1210_3225Metric,,Require effective capacitance >=4.7uF on actual rail; exact MPN/bias curve unselected
C8,100nF 50V X7R,,Capacitor_SMD:C_0805_2012Metric,,
C12,10uF 50V X7R,,Capacitor_SMD:C_1210_3225Metric,,Require effective capacitance >=4.7uF on actual rail; exact MPN/bias curve unselected
K3,G6K-2F-Y DC5,G6K-2F-Y DC5,Relay_SMD:Relay_DPDT_Omron_G6K-2F-Y,https://omronfs.omron.com/en_US/ecb/products/pdf/en-g6k.pdf,Released Master / energized Send-Return; second input-range relay remains external
J1,POST_RECEIVER,,Connector_PinHeader_2.54mm:PinHeader_1x03_P2.54mm_Vertical,,Prototype interface; final locking connector and harness not selected
J2,E03_PROCESSED_OUT,,Connector_PinHeader_2.54mm:PinHeader_1x03_P2.54mm_Vertical,,Prototype interface; final locking connector and harness not selected
J3,E02_J5_GAIN_COIL,,Connector_PinHeader_2.54mm:PinHeader_1x02_P2.54mm_Vertical,,Prototype interface; final locking connector and harness not selected
J4,REGULATED_RAILS,,Connector_PinHeader_2.54mm:PinHeader_1x05_P2.54mm_Vertical,,Prototype interface; final locking connector and harness not selected
